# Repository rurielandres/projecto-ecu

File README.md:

# Projecto-Ecu
## 👥 Autores
- **Uriel Ramirez**   
---
##  Introducción
Nuestro proyecto se centra en la restauración de ECUs (Unidades de Control Electrónico), devolviéndoles la funcionalidad y prolongando su vida útil. Además, desarrollamos sistemas de emulación analógica que permiten verificar el correcto funcionamiento de los módulos, simulando condiciones reales de motores, luces, sonido y otros componentes.

Este enfoque no solo reduce costos frente a la compra de unidades nuevas, sino que también aporta a la sostenibilidad al reutilizar y optimizar recursos electrónicos.

## ⚙️ Esquema en bloques
- Ecu
- Esp32 C3 mini x2
- buzzer
- luces leds
- Motores

##  Componentes y costos aproximados

| Componente                   | Costo (ARS) |
|------------------------------|-------------|
| ESP32 C3 super mini x2          | 20.000      |
| Batería de Lipo              | 30.040      |
| luces led      | 2.300       |
| Motores reductores   x2     | 5.100       |
| buzzer           | 4.000       |
| placa de cobre                  | 3.000      |
| **Total**                    | **84.440**  |

##  Objetivo del Proyecto

El proyecto tiene un doble objetivo principal:
Restauración de ECUs: Devolver la funcionalidad original a las Unidades de Control Electrónico (ECU) automotrices, prolongando su vida útil y ofreciendo una alternativa más sostenible y económica frente a la compra de unidades nuevas.

Desarrollo de un sistema de simulación: Crear un entorno didáctico y experimental mediante un sistema de emulación analógica (usando placas ESP32 interconectadas por WiFi) para verificar el funcionamiento de las ECUs, demostrando de forma práctica cómo estas controlan diversas funciones del vehículo, como motores, luces y sonidos.

## Esquematico

## PCB

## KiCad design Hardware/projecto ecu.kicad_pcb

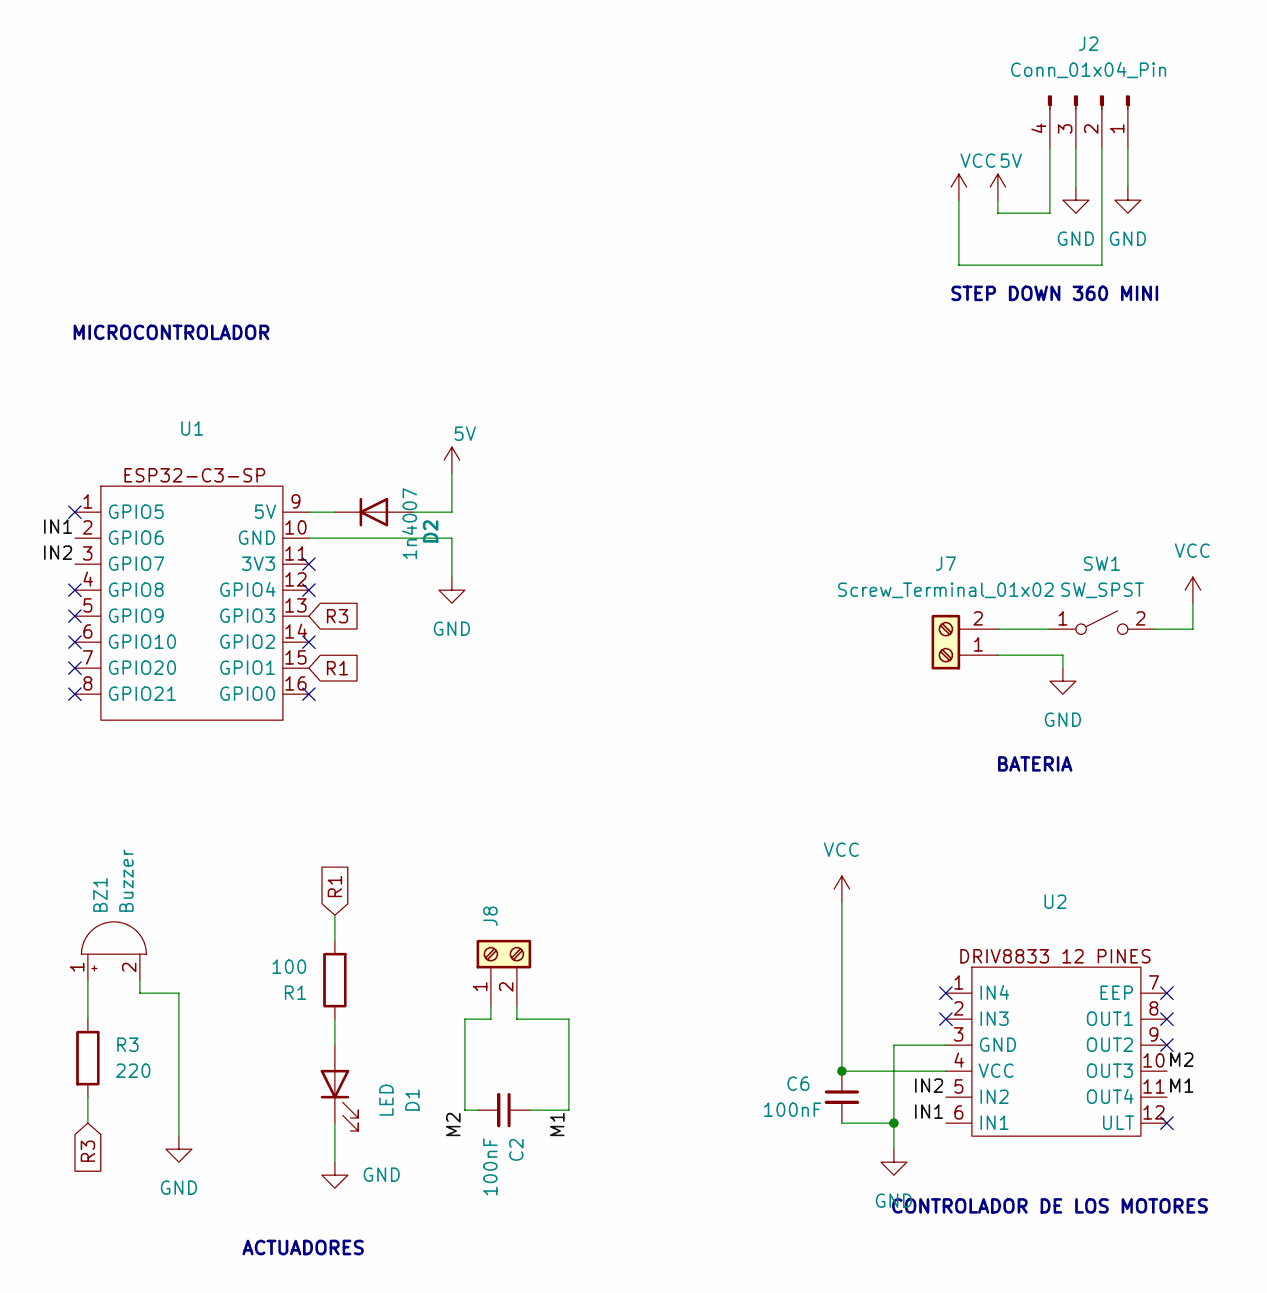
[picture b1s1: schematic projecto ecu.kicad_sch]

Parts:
BZ1: Buzzer; Buzzer_12x9.5RM7.6
C2: 100nF; C_Disc_D8.0mm_W5.0mm_P7.50mm
C6: 100nF; CP_Radial_D10.0mm_P3.50mm
D1: LED; LED_D1.8mm_W1.8mm_H2.4mm_Horizontal_O1.27mm_Z4.9mm
D2: 1n4007; C_Axial_L3.8mm_D2.6mm_P7.50mm_Horizontal
J2: Conn_01x04_Pin; Mini360_step-down
J7, J8: Screw_Terminal_01x02; TerminalBlock_MetzConnect_Type055_RT01502HDWU_1x02_P5.00mm_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
R1: 100; R_Axial_DIN0204_L3.6mm_D1.6mm_P5.08mm_Horizontal
R3: 220; R_Axial_DIN0204_L3.6mm_D1.6mm_P5.08mm_Horizontal
SW1: SW_SPST; SW_DIP_SPSTx01_Slide_6.7x4.1mm_W7.62mm_P2.54mm_LowProfile
U1: ESP32 C3 SUPER MINI
U2: drv8833

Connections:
5V: D2.2 (A), J2.4
/IN1: U1.2 (GPIO6), U2.6 (IN1)
/IN2: U1.3 (GPIO7), U2.5 (IN2)
/M1: C2.1, J8.2, U2.11 (OUT4)
/M2: C2.2, J8.1, U2.10 (OUT3)
GND: BZ1.2 (-), C6.2, D1.1 (K), J2.1, J2.3, J7.1, U1.10 (GND), U2.3 (GND)
unnamed: BZ1.1 (+), R3.1
unnamed: D1.2 (A), R1.1
unnamed: D2.1 (K), U1.9 (5V)
unnamed: J7.2, SW1.1 (A)
R1: R1.2, U1.15 (GPIO1)
R3: R3.2, U1.13 (GPIO3)
VCC: C6.1, J2.2, SW1.2 (B), U2.4 (VCC)

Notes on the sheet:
ACTUADORES
MICROCONTROLADOR
STEP DOWN 360 MINI
BATERIA
CONTROLADOR DE LOS MOTORES

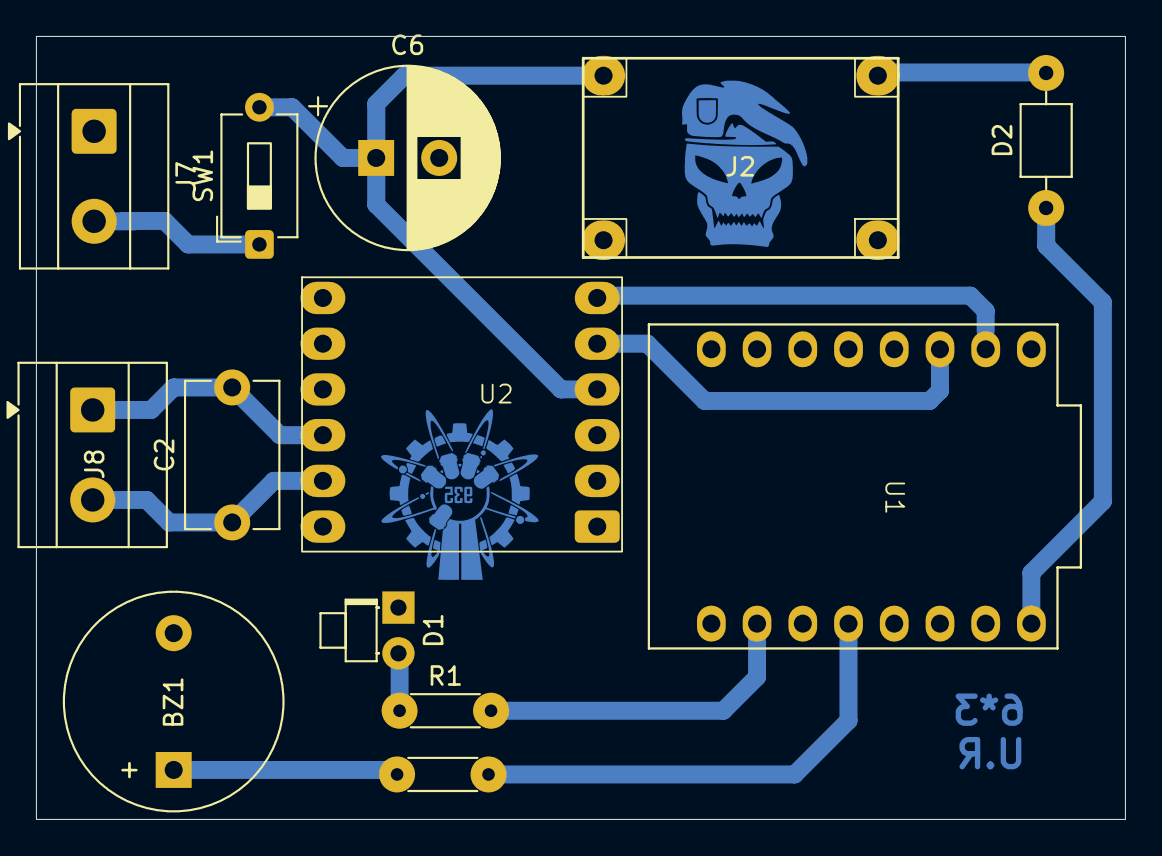
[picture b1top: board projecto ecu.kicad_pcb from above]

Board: 2 copper layers, 60.5 x 43.5 mm, 13 parts (0 on the bottom side), 13 nets.
